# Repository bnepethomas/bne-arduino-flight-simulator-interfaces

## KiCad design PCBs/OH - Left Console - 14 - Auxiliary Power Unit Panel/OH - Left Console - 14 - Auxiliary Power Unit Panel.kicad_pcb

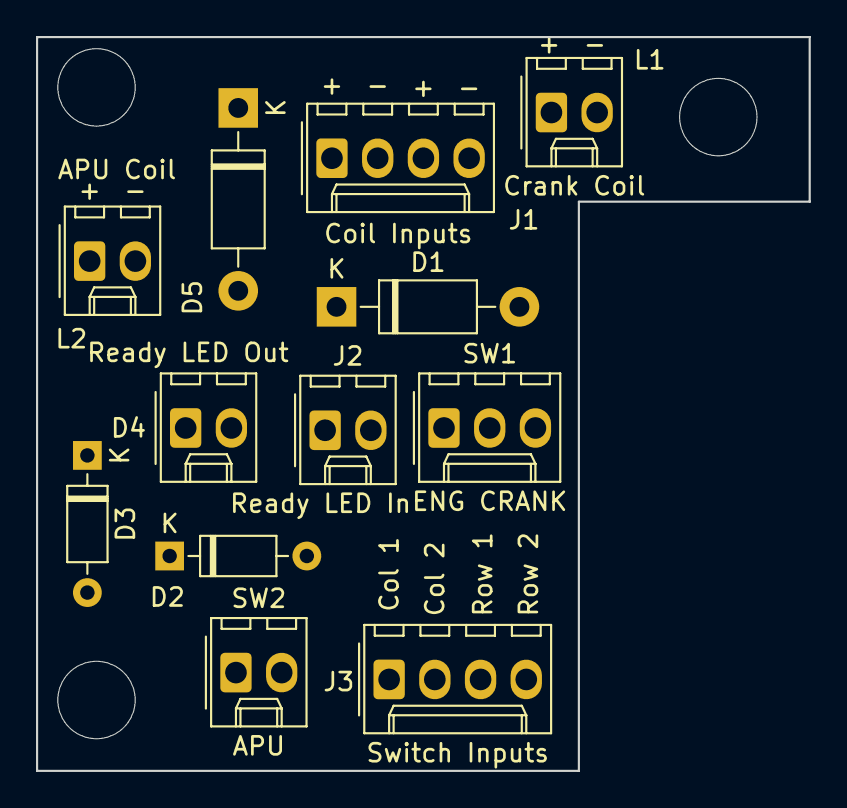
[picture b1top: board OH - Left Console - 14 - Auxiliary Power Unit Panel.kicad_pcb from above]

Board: 2 copper layers, 42.9 x 40.8 mm, 15 parts (0 on the bottom side), 12 nets, no tracks yet.

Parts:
D1, D5: D; D_DO-41_SOD81_P10.16mm_Horizontal
D2, D3: D; D_Signal_P7.62mm_Horizontal
D4: Ready LED Out; Molex_1x02_P2.54mm_Vertical
H1, H2, H3: MountingHole; MountingHole_4.3mm_M4
J1: Coil Inputs; Molex_1x04_P2.54mm_Vertical
J2: Ready LED In; Molex_1x02_P2.54mm_Vertical
J3: Switch Inputs; Molex_1x04_P2.54mm_Vertical
L1: Crank Coil; Molex_1x02_P2.54mm_Vertical
L2: APU Coil; Molex_1x02_P2.54mm_Vertical
SW1: ENG CRANK; Molex_1x03_P2.54mm_Vertical
SW2: APU; Molex_1x02_P2.54mm_Vertical

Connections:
/Col1: D2.2, J3.1
/Col2: D3.2, J3.2
/Row1: J3.3, SW1.1, SW2.2
/Row2: J3.4, SW1.3
unnamed: D1.1, J1.3, L1.1
unnamed: D1.2, J1.4, L1.2
unnamed: D2.1, SW1.2
unnamed: D3.1, SW2.1
unnamed: D4.1, J2.2
unnamed: D4.2, J2.1
unnamed: D5.1, J1.1, L2.1
unnamed: D5.2, J1.2, L2.2

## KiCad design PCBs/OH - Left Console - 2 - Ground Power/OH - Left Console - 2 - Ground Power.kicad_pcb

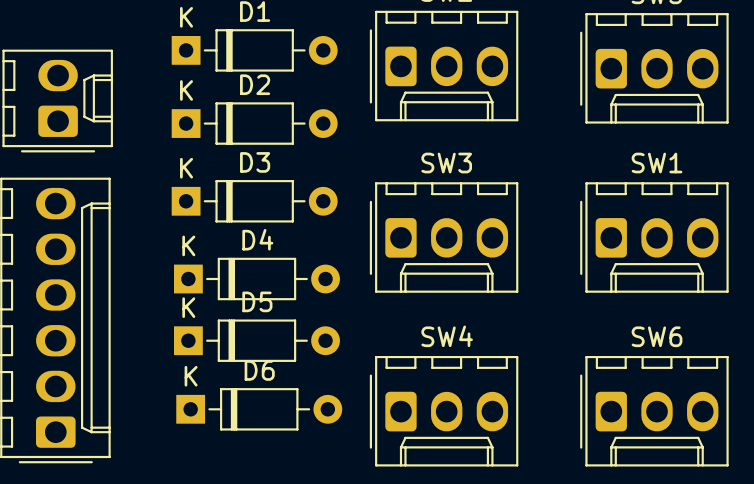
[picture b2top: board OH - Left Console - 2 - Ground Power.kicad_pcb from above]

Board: 2 copper layers, 14 parts (0 on the bottom side), 14 nets, no tracks yet.

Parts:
D1, D2, D3, D4, D5, D6: D; D_Signal_P7.62mm_Horizontal
J1: Input Columns; Molex_1x06_P2.54mm_Vertical
J2: Input Rows; Molex_1x02_P2.54mm_Vertical
SW1: EXT_PWR_SW; Molex_1x03_P2.54mm_Vertical
SW2: GND_PWR_1_SW; Molex_1x03_P2.54mm_Vertical
SW3: GND_PWR_2_SW; Molex_1x03_P2.54mm_Vertical
SW4: GND_PWR_3_SW; Molex_1x03_P2.54mm_Vertical
SW5: GND_PWR_4_SW; Molex_1x03_P2.54mm_Vertical
SW6: FIRE_TEST_SW; Molex_1x03_P2.54mm_Vertical

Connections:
unnamed: D1.1, SW1.2
unnamed: D1.2, J1.1
unnamed: D2.1, SW2.2
unnamed: D2.2, J1.2
unnamed: D3.1, SW3.2
unnamed: D3.2, J1.3
unnamed: D4.1, SW4.2
unnamed: D4.2, J1.4
unnamed: D5.1, SW5.2
unnamed: D5.2, J1.5
unnamed: D6.1, SW6.2
unnamed: D6.2, J1.6
unnamed: J2.1, SW1.1, SW2.1, SW3.1, SW4.1, SW5.1, SW6.1
unnamed: J2.2, SW1.3, SW2.3, SW3.3, SW4.3, SW5.3, SW6.3

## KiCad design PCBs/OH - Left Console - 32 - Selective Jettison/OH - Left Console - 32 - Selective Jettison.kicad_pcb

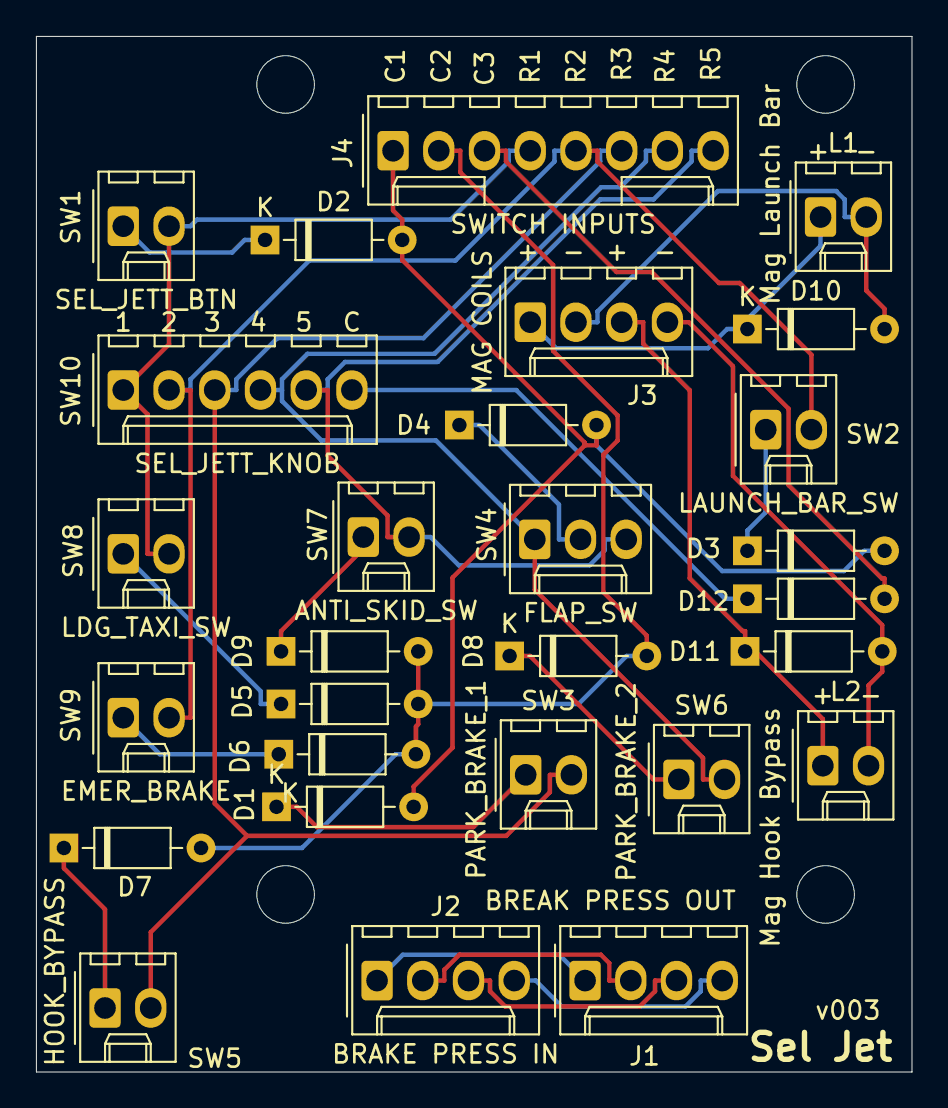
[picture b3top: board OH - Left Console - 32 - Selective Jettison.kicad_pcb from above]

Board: 2 copper layers, 48.6 x 57.5 mm, 32 parts (0 on the bottom side), 26 nets.

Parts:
D1, D2, D3, D4, D5, D6, D7, D8, D9, D10, D11, D12: D; D_Signal_P7.62mm_Horizontal
H1, H2, H3, H4: MountingHole; MountingHole_3.2mm_M3
J1: BREAK PRESS OUT; Molex_1x04_P2.54mm_Vertical
J2: BRAKE PRESS IN; Molex_1x04_P2.54mm_Vertical
J3: MAG COILS; Molex_1x04_P2.54mm_Vertical
J4: SWITCH INPUTS; Molex_1x08_P2.54mm_Vertical
L1: Mag Launch Bar; Molex_1x02_P2.54mm_Vertical
L2: Mag Hook Bypass; Molex_1x02_P2.54mm_Vertical
SW1: SEL_JETT_BTN; Molex_1x02_P2.54mm_Vertical
SW2: LAUNCH_BAR_SW; Molex_1x02_P2.54mm_Vertical
SW3: PARK_BRAKE_1; Molex_1x02_P2.54mm_Vertical
SW4: FLAP_SW; Molex_1x03_P2.54mm_Vertical
SW5: HOOK_BYPASS; Molex_1x02_P2.54mm_Vertical
SW6: PARK_BRAKE_2; Molex_1x02_P2.54mm_Vertical
SW7: ANTI_SKID_SW; Molex_1x02_P2.54mm_Vertical
SW8: LDG_TAXI_SW; Molex_1x02_P2.54mm_Vertical
SW9: EMER_BRAKE; Molex_1x02_P2.54mm_Vertical
SW10: SEL_JETT_KNOB; Molex_1x06_P2.54mm_Vertical

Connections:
/COL1: D1.2, D2.2, D3.2, D4.2, J4.1
/COL2: D5.2, D6.2, D7.2, D8.2, D9.2, J4.2
/COL3: D12.2, J4.3
/MAG_1_+: D10.1, J3.1, L1.1
/MAG_1_-: D10.2, J3.2, L1.2
/MAG_2_+: D11.1, J3.3, L2.1
/MAG_2_-: D11.2, J3.4, L2.2
/ROW1: J4.4, SW1.2, SW8.2, SW10.1
/ROW2: J4.5, SW2.2, SW9.2, SW10.2
/ROW3: J4.6, SW3.2, SW5.2, SW10.3
/ROW4: J4.7, SW4.1, SW6.2, SW10.4
/ROW5: J4.8, SW4.3, SW7.2, SW10.5
unnamed: D1.1, SW3.1
unnamed: D2.1, SW1.1
unnamed: D3.1, SW2.1
unnamed: D4.1, SW4.2
unnamed: D5.1, SW8.1
unnamed: D6.1, SW9.1
unnamed: D7.1, SW5.1
unnamed: D8.1, SW6.1
unnamed: D9.1, SW7.1
unnamed: D12.1, SW10.6
unnamed: J1.1, J2.1
unnamed: J1.2, J2.2
unnamed: J1.3, J2.3
unnamed: J1.4, J2.4

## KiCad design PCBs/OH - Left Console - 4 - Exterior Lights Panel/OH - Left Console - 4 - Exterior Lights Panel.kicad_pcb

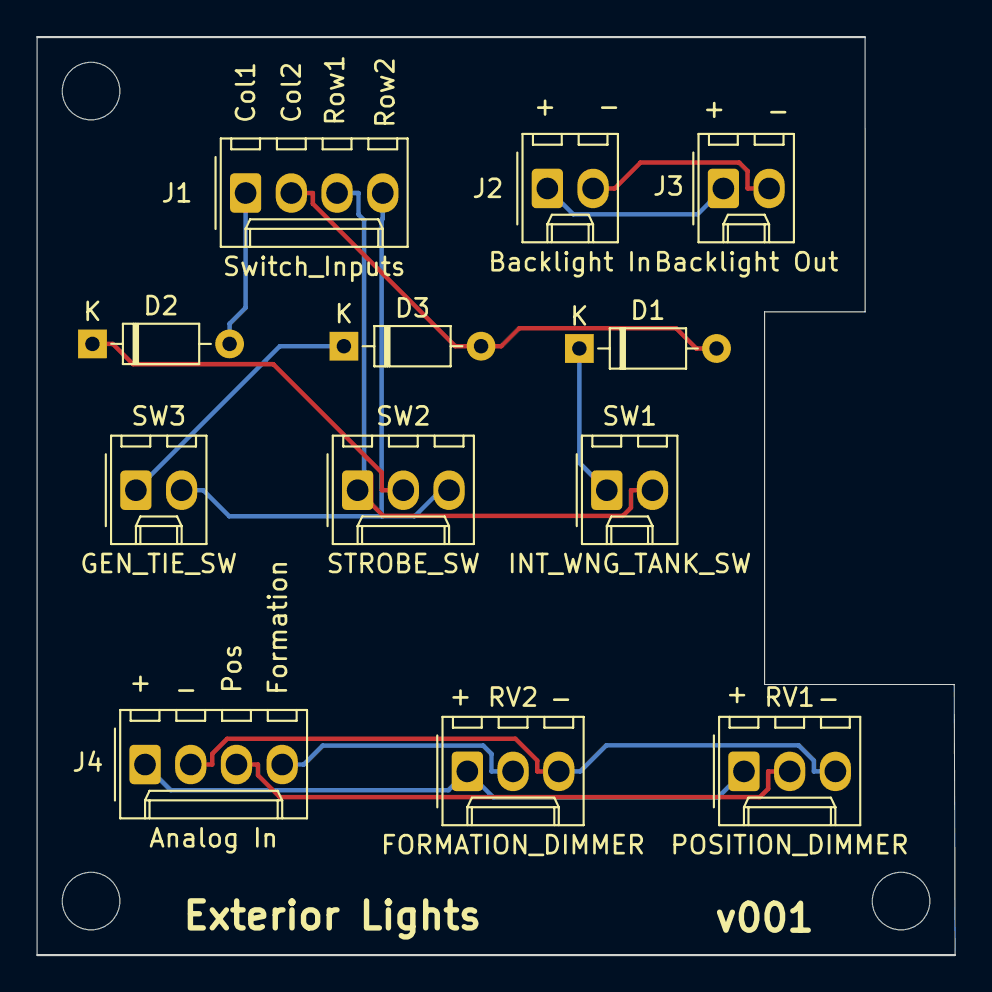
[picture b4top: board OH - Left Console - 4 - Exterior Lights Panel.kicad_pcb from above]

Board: 2 copper layers, 51.0 x 51.0 mm, 15 parts (0 on the bottom side), 13 nets.

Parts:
D1, D2, D3: D; D_Signal_P7.62mm_Horizontal
H1, H2, H3: MountingHole; MountingHole_3.2mm_M3
J1: Switch_Inputs; Molex_1x04_P2.54mm_Vertical
J2: Backlight In; Molex_1x02_P2.54mm_Vertical
J3: Backlight Out; Molex_1x02_P2.54mm_Vertical
J4: Analog In; Molex_1x04_P2.54mm_Vertical
RV1: POSITION_DIMMER; Molex_1x03_P2.54mm_Vertical
RV2: FORMATION_DIMMER; Molex_1x03_P2.54mm_Vertical
SW1: INT_WNG_TANK_SW; Molex_1x02_P2.54mm_Vertical
SW2: STROBE_SW; Molex_1x03_P2.54mm_Vertical
SW3: GEN_TIE_SW; Molex_1x02_P2.54mm_Vertical

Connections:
/Col1: D2.2, J1.1
/Col2: D1.2, D3.2, J1.2
/Row1: J1.3, SW1.2, SW2.1
/Row2: J1.4, SW2.3, SW3.2
unnamed: D1.1, SW1.1
unnamed: D2.1, SW2.2
unnamed: D3.1, SW3.1
unnamed: J2.1, J3.1
unnamed: J2.2, J3.2
unnamed: J4.1, RV1.1, RV2.1
unnamed: J4.2, RV1.3, RV2.3
unnamed: J4.3, RV1.2
unnamed: J4.4, RV2.2

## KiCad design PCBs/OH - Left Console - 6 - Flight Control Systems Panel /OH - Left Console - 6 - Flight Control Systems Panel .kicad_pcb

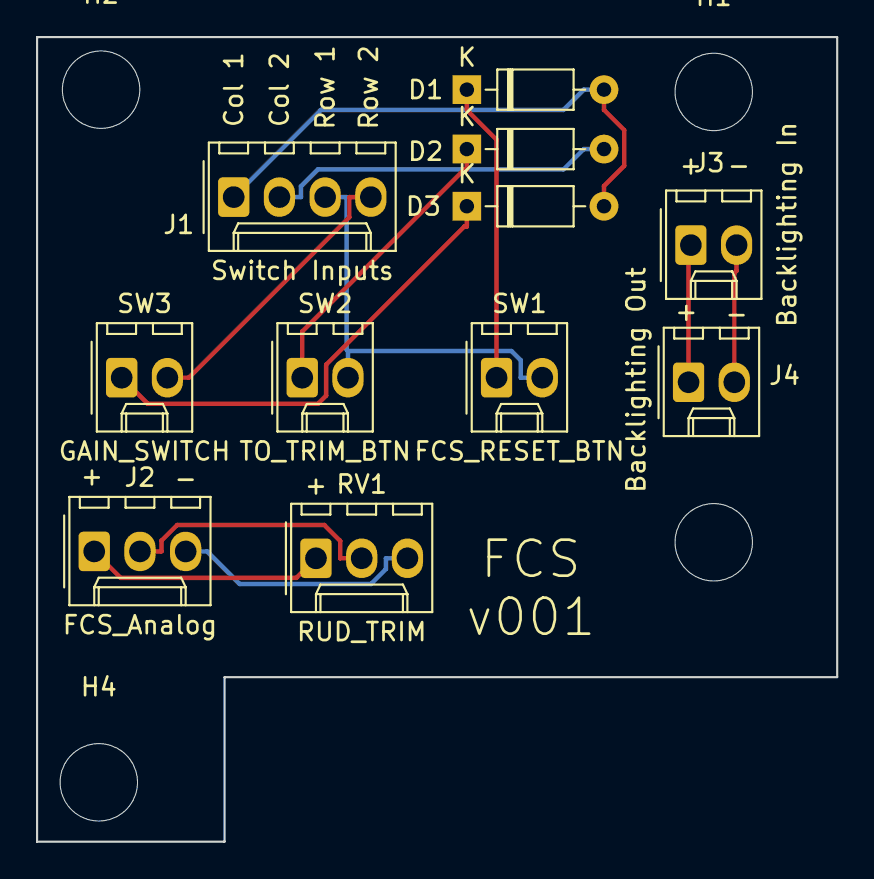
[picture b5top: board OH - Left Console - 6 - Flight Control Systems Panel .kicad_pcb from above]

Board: 2 copper layers, 44.5 x 44.7 mm, 15 parts (0 on the bottom side), 12 nets.

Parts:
D1, D2, D3: D; D_DO-35_SOD27_P7.62mm_Horizontal
H1, H2, H3, H4: MountingHole; MountingHole_4.3mm_M4
J1: Switch Inputs; Molex_1x04_P2.54mm_Vertical
J2: FCS_Analog; Molex_1x03_P2.54mm_Vertical
J3: Backlighting In; Molex_1x02_P2.54mm_Vertical
J4: Backlighting Out; Molex_1x02_P2.54mm_Vertical
RV1: RUD_TRIM; Molex_1x03_P2.54mm_Vertical
SW1: FCS_RESET_BTN; Molex_1x02_P2.54mm_Vertical
SW2: TO_TRIM_BTN; Molex_1x02_P2.54mm_Vertical
SW3: GAIN_SWITCH; Molex_1x02_P2.54mm_Vertical

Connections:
/Backlight+: J3.1, J4.1
/Backlight-: J3.2, J4.2
/Col1: D1.2, D3.2, J1.1
/Col2: D2.2, J1.2
/Row1: J1.3, SW1.2, SW2.2
/Row2: J1.4, SW3.2
unnamed: D1.1, SW1.1
unnamed: D2.1, SW2.1
unnamed: D3.1, SW3.1
unnamed: J2.1, RV1.1
unnamed: J2.2, RV1.2
unnamed: J2.3, RV1.3

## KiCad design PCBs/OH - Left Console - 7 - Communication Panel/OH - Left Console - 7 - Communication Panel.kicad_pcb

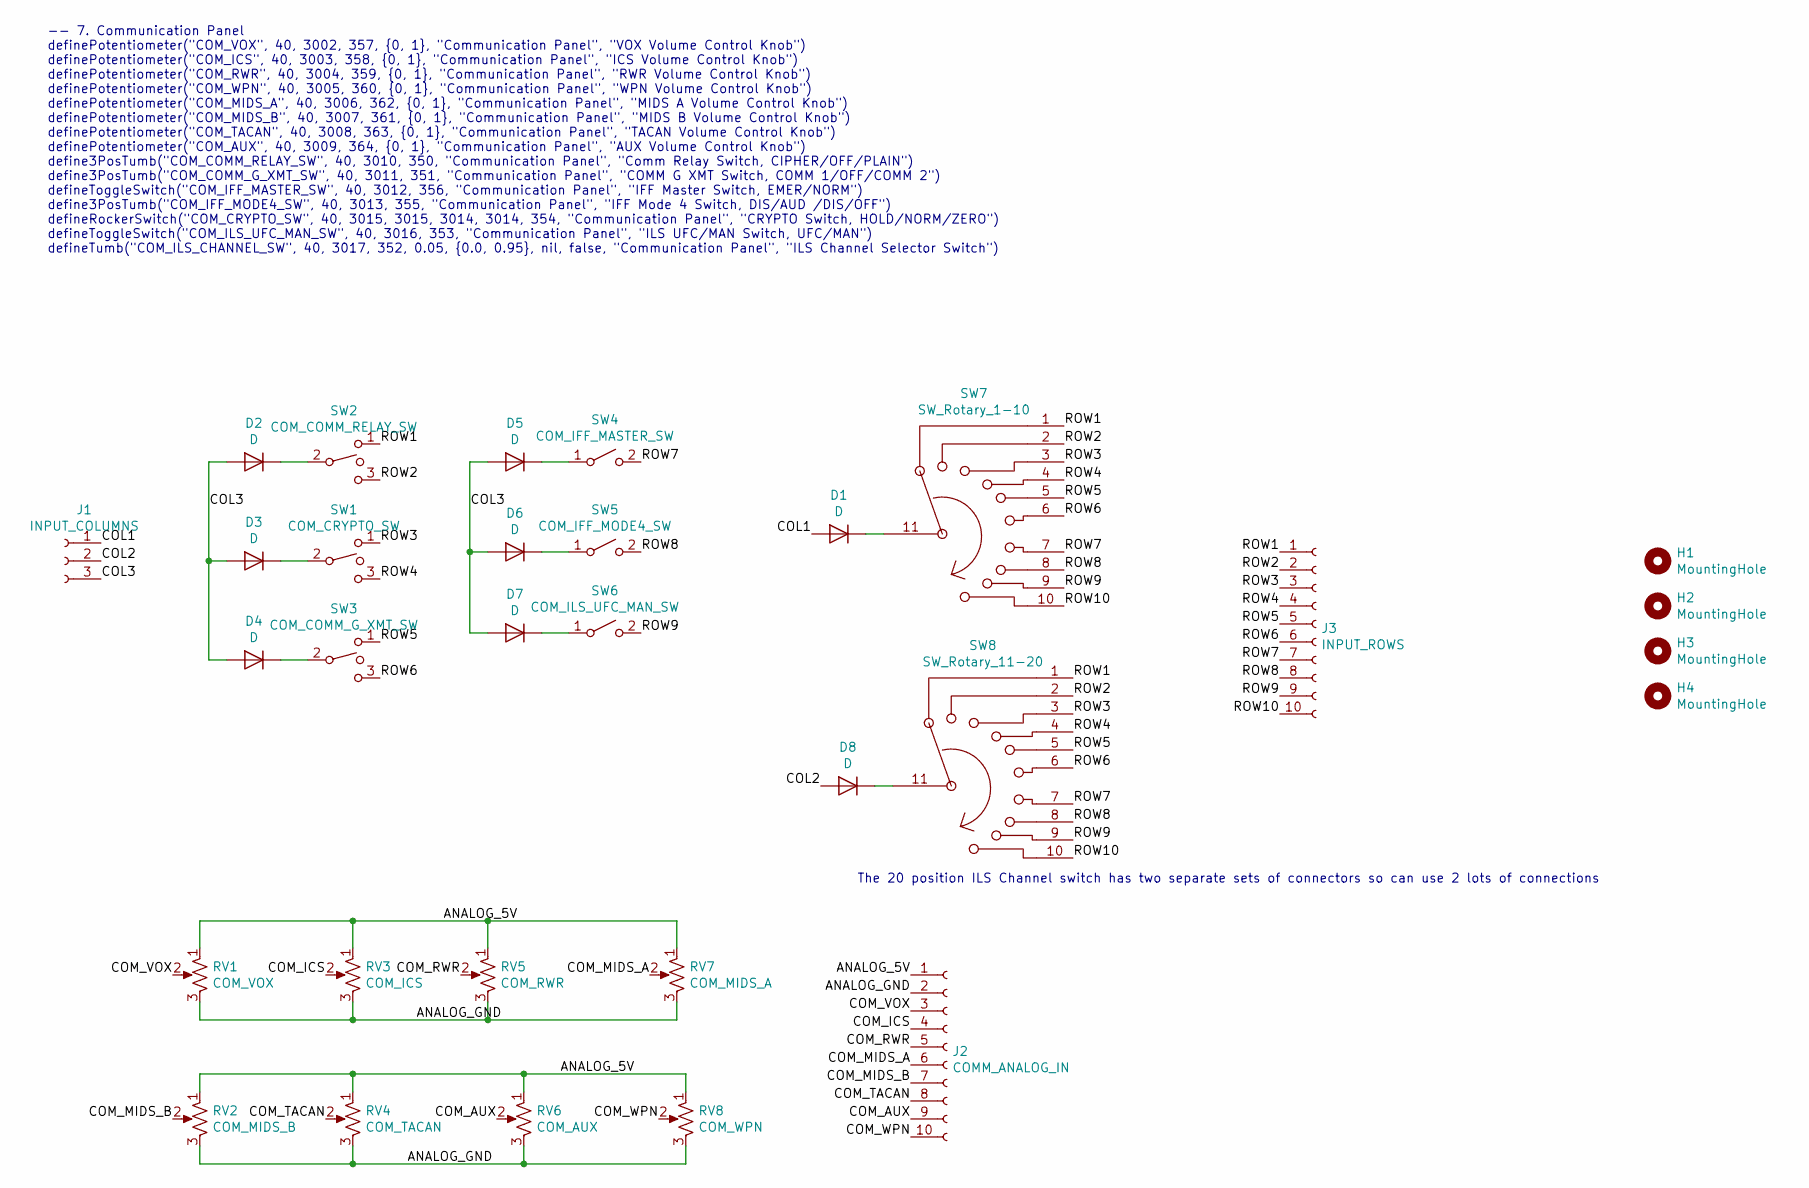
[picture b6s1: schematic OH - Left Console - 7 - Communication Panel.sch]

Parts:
D1, D2, D3, D4, D5, D6, D7, D8: D; D_Signal_P7.62mm_Horizontal
H1, H2, H3, H4: MountingHole; MountingHole_3.2mm_M3
J1: INPUT_COLUMNS; Molex_1x03_P2.54mm_Vertical
J2: COMM_ANALOG_IN; Molex_1x10_P2.54mm_Vertical
J3: INPUT_ROWS; Molex_1x10_P2.54mm_Vertical
RV1: COM_VOX; Molex_1x03_P2.54mm_Vertical
RV2: COM_MIDS_B; Molex_1x03_P2.54mm_Vertical
RV3: COM_ICS; Molex_1x03_P2.54mm_Vertical
RV4: COM_TACAN; Molex_1x03_P2.54mm_Vertical
RV5: COM_RWR; Molex_1x03_P2.54mm_Vertical
RV6: COM_AUX; Molex_1x03_P2.54mm_Vertical
RV7: COM_MIDS_A; Molex_1x03_P2.54mm_Vertical
RV8: COM_WPN; Molex_1x03_P2.54mm_Vertical
SW1: COM_CRYPTO_SW; Molex_1x03_P2.54mm_Vertical
SW2: COM_COMM_RELAY_SW; Molex_1x03_P2.54mm_Vertical
SW3: COM_COMM_G_XMT_SW; Molex_1x03_P2.54mm_Vertical
SW4: COM_IFF_MASTER_SW; Molex_1x02_P2.54mm_Vertical
SW5: COM_IFF_MODE4_SW; Molex_1x02_P2.54mm_Vertical
SW6: COM_ILS_UFC_MAN_SW; Molex_1x02_P2.54mm_Vertical
SW7: SW_Rotary_1-10; Molex_KK-254_AE-6410-12A_1x12_P2.54mm_Vertical
SW8: SW_Rotary_11-20; Molex_KK-254_AE-6410-12A_1x12_P2.54mm_Vertical

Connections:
/ANALOG_5V: J2.1, RV1.1, RV2.1, RV3.1, RV4.1, RV5.1, RV6.1, RV7.1, RV8.1
/ANALOG_GND: J2.2, RV1.3, RV2.3, RV3.3, RV4.3, RV5.3, RV6.3, RV7.3, RV8.3
/COL1: D1.2 (A), J1.1
/COL2: D8.2 (A), J1.2
/COL3: D2.2 (A), D3.2 (A), D4.2 (A), D5.2 (A), D6.2 (A), D7.2 (A), J1.3
/COM_AUX: J2.9, RV6.2
/COM_ICS: J2.4, RV3.2
/COM_MIDS_A: J2.6, RV7.2
/COM_MIDS_B: J2.7, RV2.2
/COM_RWR: J2.5, RV5.2
/COM_TACAN: J2.8, RV4.2
/COM_VOX: J2.3, RV1.2
/COM_WPN: J2.10, RV8.2
/ROW1: J3.1, SW2.1, SW7.1, SW8.1
/ROW2: J3.2, SW2.3, SW7.2, SW8.2
/ROW3: J3.3, SW1.1, SW7.3, SW8.3
/ROW4: J3.4, SW1.3, SW7.4, SW8.4
/ROW5: J3.5, SW3.1, SW7.5, SW8.5
/ROW6: J3.6, SW3.3, SW7.6, SW8.6
/ROW7: J3.7, SW4.2 (B), SW7.7, SW8.7
/ROW8: J3.8, SW5.2 (B), SW7.8, SW8.8
/ROW9: J3.9, SW6.2 (B), SW7.9, SW8.9
/ROW10: J3.10, SW7.10, SW8.10
unnamed: D1.1 (K), SW7.11
unnamed: D2.1 (K), SW2.2
unnamed: D3.1 (K), SW1.2
unnamed: D4.1 (K), SW3.2
unnamed: D5.1 (K), SW4.1 (A)
unnamed: D6.1 (K), SW5.1 (A)
unnamed: D7.1 (K), SW6.1 (A)
unnamed: D8.1 (K), SW8.11

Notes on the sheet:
-- 7. Communication Panel definePotentiometer("COM_VOX", 40, 3002, 357, {0, 1}, "Communication Panel", "VOX Volume Control Knob") definePotentiometer("COM_ICS", 40, 3003, 358, {0, 1}, "Communication Panel", "ICS Volume Control Knob") definePotentiometer("COM_RWR", 40, 3004, 359, {0, 1}, "Communicat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
The 20 position ILS Channel switch has two separate sets of connectors so can use 2 lots of connections

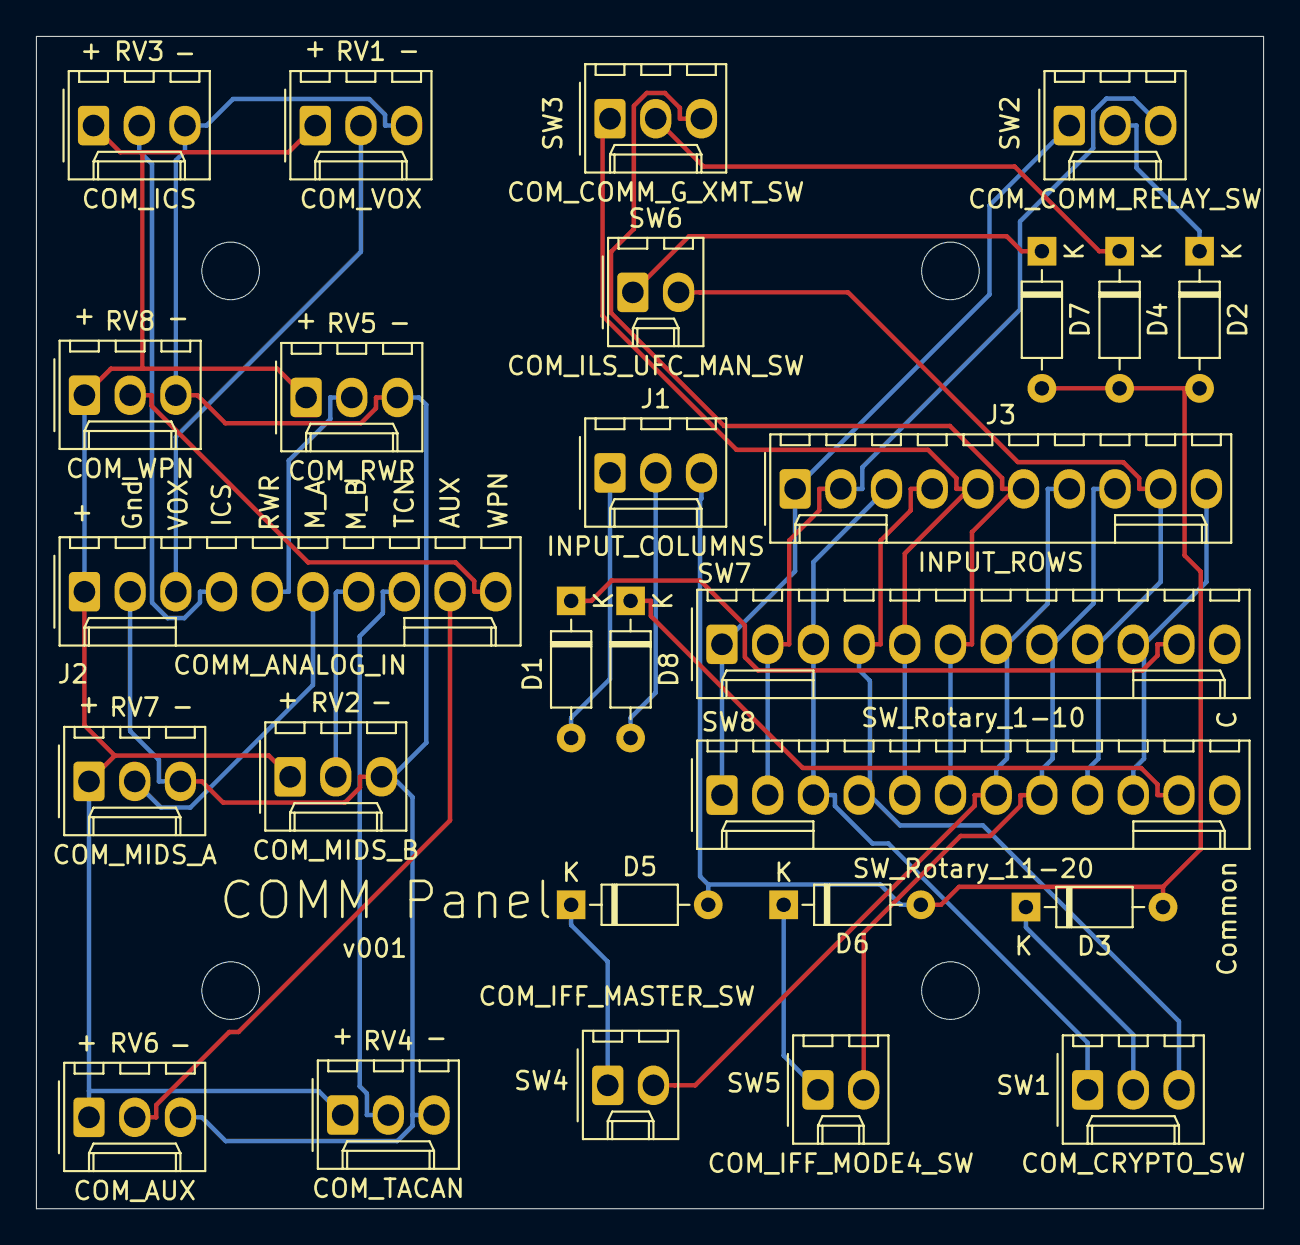
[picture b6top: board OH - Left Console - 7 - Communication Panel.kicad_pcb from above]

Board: 2 copper layers, 68.2 x 65.2 mm, 31 parts (0 on the bottom side), 31 nets.
